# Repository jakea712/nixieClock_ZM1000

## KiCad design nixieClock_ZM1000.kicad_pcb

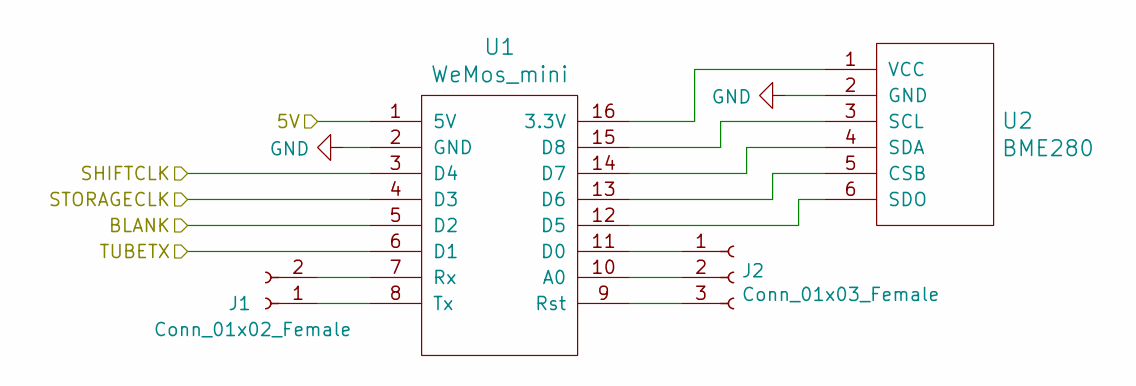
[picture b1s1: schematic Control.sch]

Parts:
J1: Conn_01x02_Female; PinHeader_1x02_P2.54mm_Vertical
J2: Conn_01x03_Female; PinHeader_1x03_P2.54mm_Vertical
U1: WeMos_mini; D1_mini_board
U2: BME280

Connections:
unnamed: J1.1, U1.8 (Tx)
unnamed: J1.2, U1.7 (Rx)
unnamed: J2.1, U1.11 (D0)
unnamed: J2.2, U1.10 (A0)
unnamed: J2.3, U1.9 (Rst)
unnamed: U1.12 (D5), U2.6 (SDO)
unnamed: U1.13 (D6), U2.5 (CSB)
unnamed: U1.14 (D7), U2.4 (SDA)
unnamed: U1.15 (D8), U2.3 (SCL)
unnamed: U1.16 (3.3V), U2.1 (VCC)

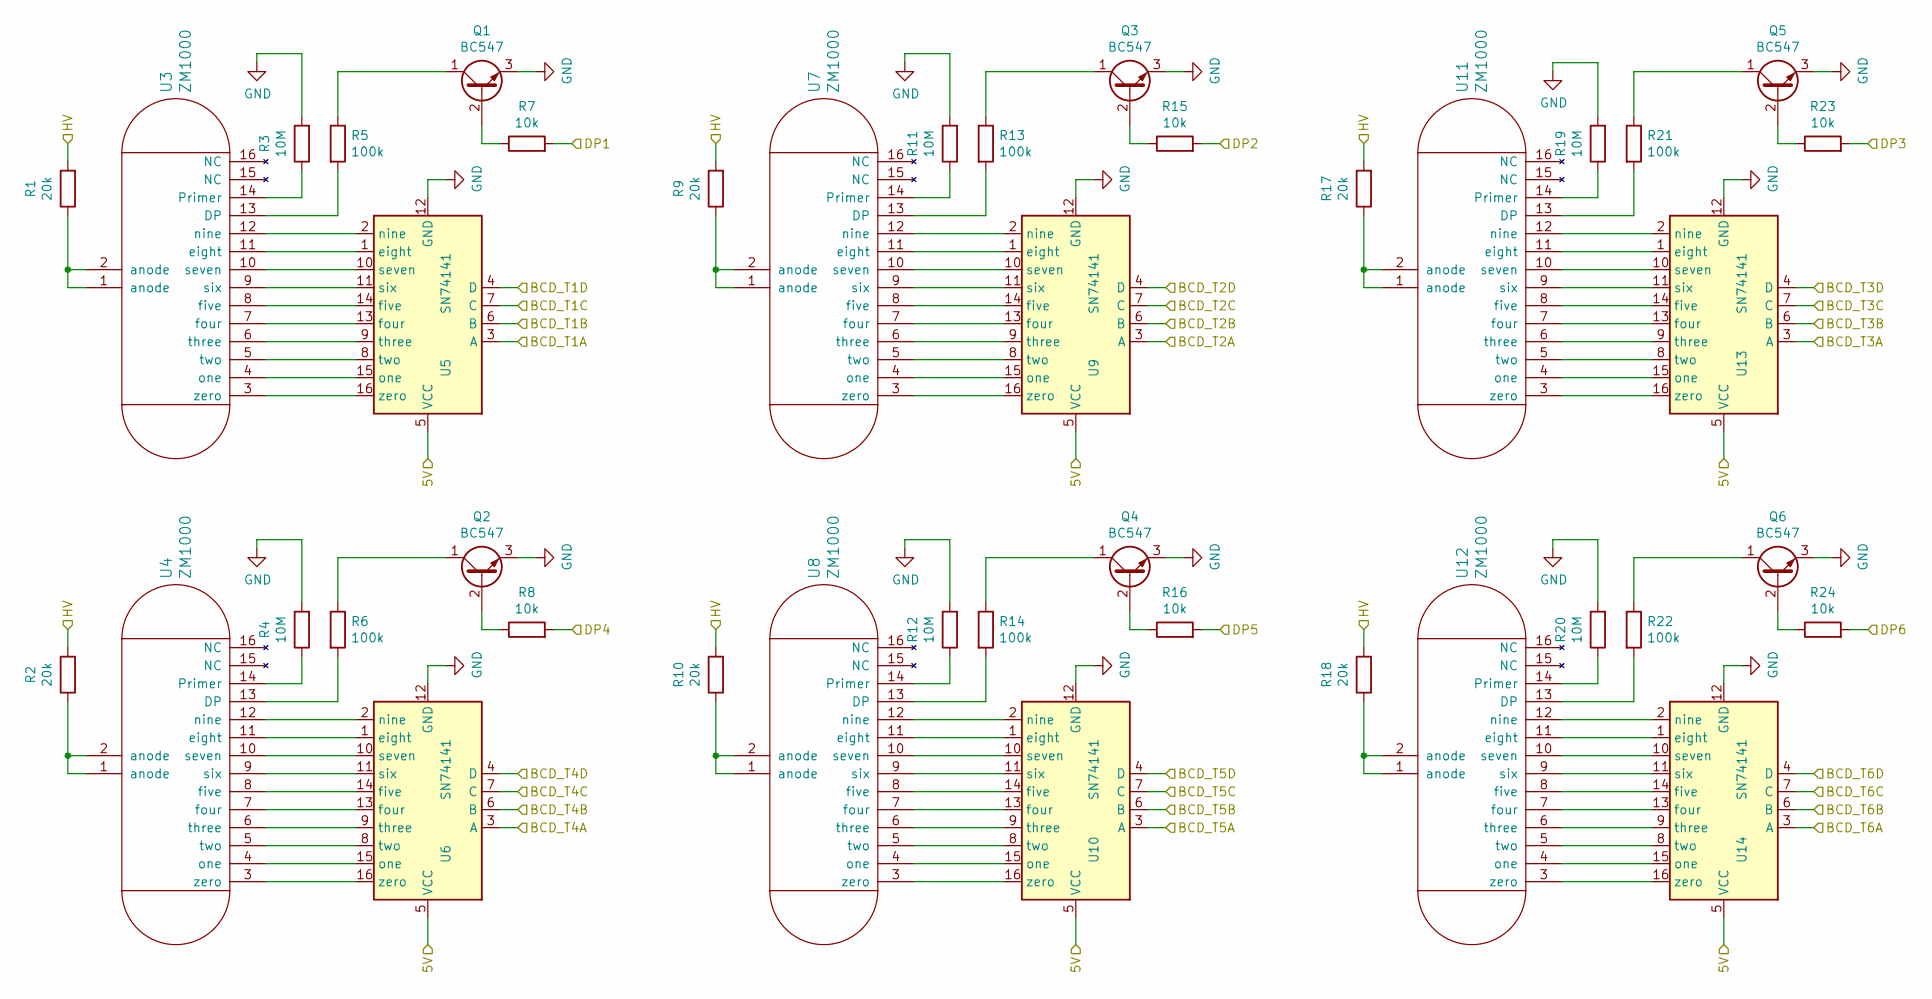
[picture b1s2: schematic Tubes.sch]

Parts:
Q1, Q2, Q3, Q4, Q5, Q6: BC547; TO-92_Inline
R1, R2, R9, R10, R17, R18: 20k; R_Axial_DIN0207_L6.3mm_D2.5mm_P10.16mm_Horizontal
R3, R4, R11, R12, R19, R20: 10M; R_Axial_DIN0207_L6.3mm_D2.5mm_P10.16mm_Horizontal
R5, R6, R13, R14, R21, R22: 100k; R_Axial_DIN0207_L6.3mm_D2.5mm_P10.16mm_Horizontal
R7, R8, R15, R16, R23, R24: 10k; R_Axial_DIN0207_L6.3mm_D2.5mm_P10.16mm_Horizontal
U3, U4, U7, U8, U11, U12: ZM1000; Nixie_ZM1000
U5, U6, U9, U10, U13, U14: SN74141; DIP-16_W7.62mm

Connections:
/PSU/HV: R1.2, R2.2, R9.2, R10.2, R17.2, R18.2; also elsewhere on the board
/Shift Registers/BCD_T1A: U5.3 (A); also elsewhere on the board
/Shift Registers/BCD_T1B: U5.6 (B); also elsewhere on the board
/Shift Registers/BCD_T1C: U5.7 (C); also elsewhere on the board
/Shift Registers/BCD_T1D: U5.4 (D); also elsewhere on the board
/Shift Registers/BCD_T2A: U9.3 (A); also elsewhere on the board
/Shift Registers/BCD_T2B: U9.6 (B); also elsewhere on the board
/Shift Registers/BCD_T2C: U9.7 (C); also elsewhere on the board
/Shift Registers/BCD_T2D: U9.4 (D); also elsewhere on the board
/Shift Registers/BCD_T3A: U13.3 (A); also elsewhere on the board
/Shift Registers/BCD_T3B: U13.6 (B); also elsewhere on the board
/Shift Registers/BCD_T3C: U13.7 (C); also elsewhere on the board
/Shift Registers/BCD_T3D: U13.4 (D); also elsewhere on the board
/Shift Registers/BCD_T4A: U6.3 (A); also elsewhere on the board
/Shift Registers/BCD_T4B: U6.6 (B); also elsewhere on the board
/Shift Registers/BCD_T4C: U6.7 (C); also elsewhere on the board
/Shift Registers/BCD_T4D: U6.4 (D); also elsewhere on the board
/Shift Registers/BCD_T5A: U10.3 (A); also elsewhere on the board
/Shift Registers/BCD_T5B: U10.6 (B); also elsewhere on the board
/Shift Registers/BCD_T5C: U10.7 (C); also elsewhere on the board
/Shift Registers/BCD_T5D: U10.4 (D); also elsewhere on the board
/Shift Registers/BCD_T6A: U14.3 (QD); also elsewhere on the board
/Shift Registers/BCD_T6B: U14.6 (QG); also elsewhere on the board
/Shift Registers/BCD_T6C: U14.7 (QH); also elsewhere on the board
/Shift Registers/BCD_T6D: U14.4 (QE); also elsewhere on the board
/Shift Registers/DP1: R7.2; also elsewhere on the board
/Shift Registers/DP2: R15.2; also elsewhere on the board
/Shift Registers/DP3: R23.2; also elsewhere on the board
/Shift Registers/DP4: R8.2; also elsewhere on the board
/Shift Registers/DP5: R16.2; also elsewhere on the board
/Shift Registers/DP6: R24.2; also elsewhere on the board
unnamed: Q1.1 (C), R5.1
unnamed: Q1.2 (B), R7.1
unnamed: Q2.1 (C), R6.1
unnamed: Q2.2 (B), R8.1
unnamed: Q3.1 (C), R13.1
unnamed: Q3.2 (B), R15.1
unnamed: Q4.1 (C), R14.1
unnamed: Q4.2 (B), R16.1
unnamed: Q5.1 (C), R21.1
unnamed: Q5.2 (B), R23.1
unnamed: Q6.1 (C), R22.1
unnamed: Q6.2 (B), R24.1
unnamed: R1.1, U3.1 (anode), U3.2 (anode)
unnamed: R2.1, U4.1 (anode), U4.2 (anode)
unnamed: R3.1, U3.14 (Primer)
unnamed: R4.1, U4.14 (Primer)
unnamed: R5.2, U3.13 (DP)
unnamed: R6.2, U4.13 (DP)
unnamed: R9.1, U7.1 (anode), U7.2 (anode)
unnamed: R10.1, U8.1 (anode), U8.2 (anode)
unnamed: R11.1, U7.14 (Primer)
unnamed: R12.1, U8.14 (Primer)
unnamed: R13.2, U7.13 (DP)
unnamed: R14.2, U8.13 (DP)
unnamed: R17.1, U11.1 (anode), U11.2 (anode)
unnamed: R18.1, U12.1 (anode), U12.2 (anode)
unnamed: R19.1, U11.14 (Primer)
unnamed: R20.1, U12.14 (Primer)
unnamed: R21.2, U11.13 (DP)
unnamed: R22.2, U12.13 (DP)
unnamed: U3.3 (zero), U5.16 (zero)
unnamed: U3.4 (one), U5.15 (one)
unnamed: U3.5 (two), U5.8 (two)
unnamed: U3.6 (three), U5.9 (three)
unnamed: U3.7 (four), U5.13 (four)
unnamed: U3.8 (five), U5.14 (five)
unnamed: U3.9 (six), U5.11 (six)
unnamed: U3.10 (seven), U5.10 (seven)
unnamed: U3.11 (eight), U5.1 (eight)
unnamed: U3.12 (nine), U5.2 (nine)
unnamed: U4.3 (zero), U6.16 (zero)
unnamed: U4.4 (one), U6.15 (one)
unnamed: U4.5 (two), U6.8 (two)
unnamed: U4.6 (three), U6.9 (three)
unnamed: U4.7 (four), U6.13 (four)
unnamed: U4.8 (five), U6.14 (five)
unnamed: U4.9 (six), U6.11 (six)
unnamed: U4.10 (seven), U6.10 (seven)
unnamed: U4.11 (eight), U6.1 (eight)
unnamed: U4.12 (nine), U6.2 (nine)
unnamed: U7.3 (zero), U9.16 (zero)
unnamed: U7.4 (one), U9.15 (one)
unnamed: U7.5 (two), U9.8 (two)
unnamed: U7.6 (three), U9.9 (three)
unnamed: U7.7 (four), U9.13 (four)
unnamed: U7.8 (five), U9.14 (five)
unnamed: U7.9 (six), U9.11 (six)
unnamed: U7.10 (seven), U9.10 (seven)
unnamed: U7.11 (eight), U9.1 (eight)
unnamed: U7.12 (nine), U9.2 (nine)
unnamed: U8.11 (eight), U10.1 (eight)
unnamed: U8.12 (nine), U10.2 (nine)
unnamed: U8.5 (two), U10.8 (two)
unnamed: U8.6 (three), U10.9 (three)
unnamed: U8.10 (seven), U10.10 (seven)
unnamed: U8.9 (six), U10.11 (six)
unnamed: U8.7 (four), U10.13 (four)
unnamed: U8.8 (five), U10.14 (five)
unnamed: U8.4 (one), U10.15 (one)
unnamed: U8.3 (zero), U10.16 (zero)
unnamed: U11.3 (zero), U13.16 (zero)
unnamed: U11.4 (one), U13.15 (one)
unnamed: U11.5 (two), U13.8 (two)
unnamed: U11.6 (three), U13.9 (three)
unnamed: U11.7 (four), U13.13 (four)
unnamed: U11.8 (five), U13.14 (five)
unnamed: U11.9 (six), U13.11 (six)
unnamed: U11.10 (seven), U13.10 (seven)
unnamed: U11.11 (eight), U13.1 (eight)
unnamed: U11.12 (nine), U13.2 (nine)
unnamed: U12.4 (one), U14.15 (QA)
unnamed: U12.8 (five), U14.14 (SER)
unnamed: U12.11 (eight), U14.1 (QB)
unnamed: U12.12 (nine), U14.2 (QC)

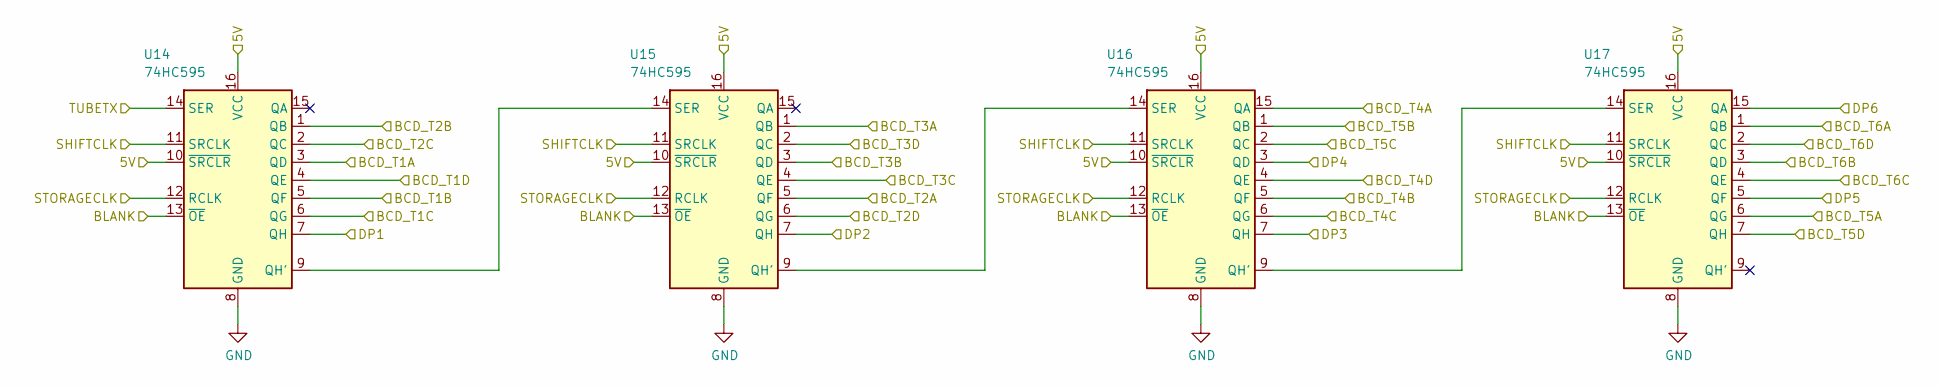
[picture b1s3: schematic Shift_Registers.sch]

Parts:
U14, U15, U16, U17: 74HC595; SOIC-16_3.9x9.9mm_P1.27mm

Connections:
/Shift Registers/BCD_T1A: U15.3 (QD); also elsewhere on the board
/Shift Registers/BCD_T1B: U15.5 (QF); also elsewhere on the board
/Shift Registers/BCD_T1C: U15.6 (QG); also elsewhere on the board
/Shift Registers/BCD_T1D: U15.4 (QE); also elsewhere on the board
/Shift Registers/BCD_T2A: U16.5 (QF); also elsewhere on the board
/Shift Registers/BCD_T2B: U15.1 (QB); also elsewhere on the board
/Shift Registers/BCD_T2C: U15.2 (QC); also elsewhere on the board
/Shift Registers/BCD_T2D: U16.6 (QG); also elsewhere on the board
/Shift Registers/BCD_T3A: U16.1 (QB); also elsewhere on the board
/Shift Registers/BCD_T3B: U16.3 (QD); also elsewhere on the board
/Shift Registers/BCD_T3C: U16.4 (QE); also elsewhere on the board
/Shift Registers/BCD_T3D: U16.2 (QC); also elsewhere on the board
/Shift Registers/BCD_T4A: U17.15 (QA); also elsewhere on the board
/Shift Registers/BCD_T4B: U17.5 (QF); also elsewhere on the board
/Shift Registers/BCD_T4C: U17.6 (QG); also elsewhere on the board
/Shift Registers/BCD_T4D: U17.4 (QE); also elsewhere on the board
/Shift Registers/BCD_T5B: U17.1 (QB); also elsewhere on the board
/Shift Registers/BCD_T5C: U17.2 (QC); also elsewhere on the board
/Shift Registers/BCD_T6A: U14.3 (QD); also elsewhere on the board
/Shift Registers/BCD_T6B: U14.6 (QG); also elsewhere on the board
/Shift Registers/BCD_T6C: U14.7 (QH); also elsewhere on the board
/Shift Registers/BCD_T6D: U14.4 (QE); also elsewhere on the board
/Shift Registers/DP1: U15.7 (QH); also elsewhere on the board
/Shift Registers/DP2: U16.7 (QH); also elsewhere on the board
/Shift Registers/DP3: U17.7 (QH); also elsewhere on the board
/Shift Registers/DP4: U17.3 (QD); also elsewhere on the board
unnamed 132: U14.15 (QA); also elsewhere on the board
unnamed 133: U14.14 (SER); also elsewhere on the board
unnamed 134: U14.1 (QB); also elsewhere on the board
unnamed 135: U14.2 (QC); also elsewhere on the board
unnamed: U15.9 (QH'), U16.14 (SER)
unnamed: U16.9 (QH'), U17.14 (SER)
unnamed 140: U17.9 (QH'); also elsewhere on the board

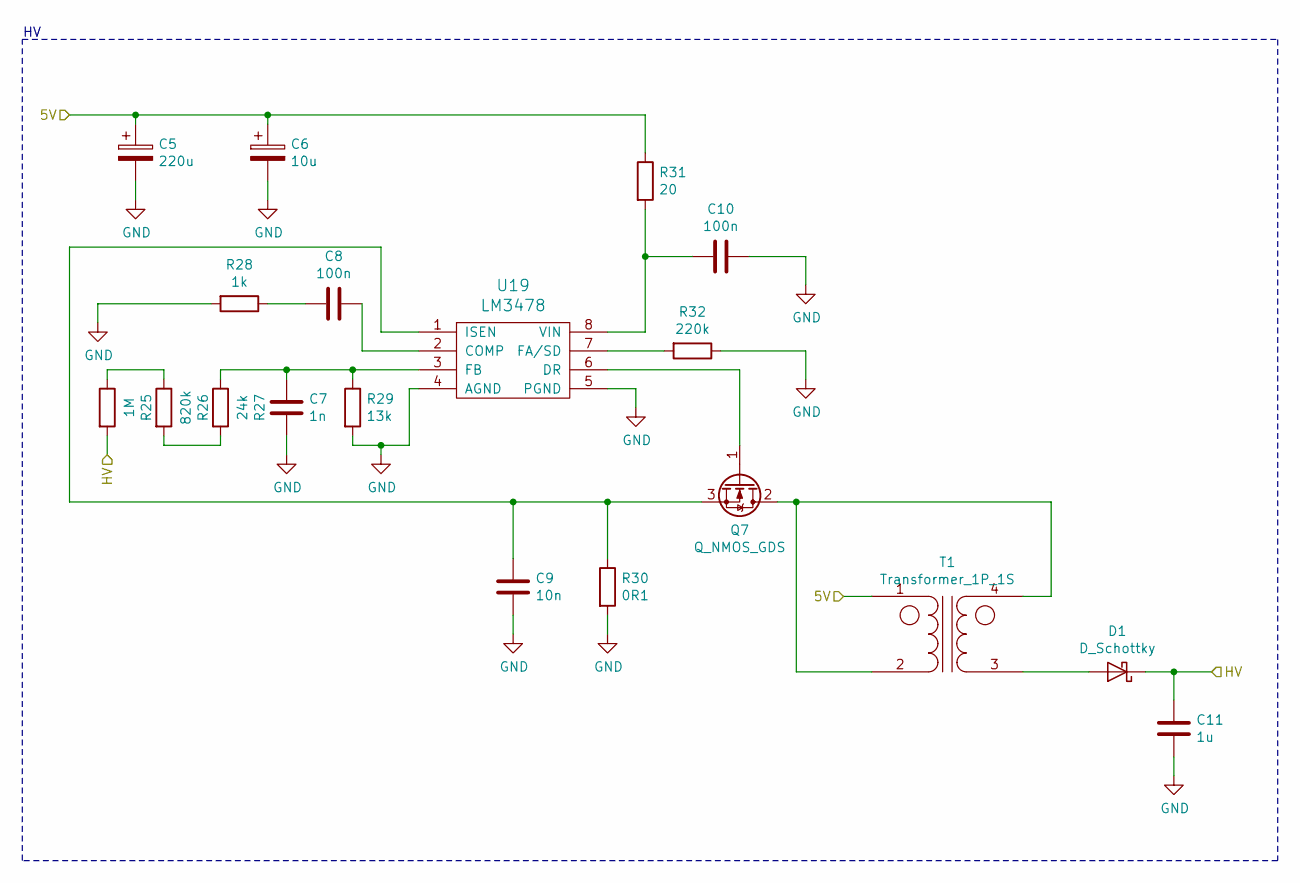
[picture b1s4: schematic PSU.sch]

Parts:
C5: 220u; CP_Radial_D5.0mm_P2.00mm
C6: 10u; CP_Radial_D4.0mm_P1.50mm
C7: 1n; C_Disc_D3.8mm_W2.6mm_P2.50mm
C8: 100n; C_Disc_D3.8mm_W2.6mm_P2.50mm
C9: 10n; C_Disc_D3.8mm_W2.6mm_P2.50mm
C10: 100n; C_Disc_D5.0mm_W2.5mm_P2.50mm
C11: 1u; CP_Radial_D6.3mm_P2.50mm
D1: D_Schottky; D_DO-41_SOD81_P10.16mm_Horizontal
Q7: Q_NMOS_GDS; TO-220-3_Horizontal_TabDown
R25: 1M; R_Axial_DIN0207_L6.3mm_D2.5mm_P10.16mm_Horizontal
R26: 820k; R_Axial_DIN0207_L6.3mm_D2.5mm_P10.16mm_Horizontal
R27: 24k; R_Axial_DIN0207_L6.3mm_D2.5mm_P10.16mm_Horizontal
R28: 1k; R_Axial_DIN0207_L6.3mm_D2.5mm_P10.16mm_Horizontal
R29: 13k; R_Axial_DIN0207_L6.3mm_D2.5mm_P10.16mm_Horizontal
R30: 0R1; R_Axial_DIN0207_L6.3mm_D2.5mm_P10.16mm_Horizontal
R31: 20; R_Axial_DIN0207_L6.3mm_D2.5mm_P10.16mm_Horizontal
R32: 220k; R_Axial_DIN0207_L6.3mm_D2.5mm_P10.16mm_Horizontal
T1: Transformer_1P_1S; Transformer_LPR6235
U19: LM3478; VSSOP-8_3.0x3.0mm_P0.65mm

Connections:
/PSU/HV: C11.1, D1.1 (K), R25.2; also elsewhere on the board
unnamed: C7.1, R27.1, R29.1, U19.3 (FB)
unnamed: C8.1, U19.2 (COMP)
unnamed: C8.2, R28.1
unnamed: C9.1, Q7.3 (S), R30.1, U19.1 (ISEN)
unnamed: C10.2, R31.2, U19.8 (VIN)
unnamed: D1.2 (A), T1.3 (SA)
unnamed: Q7.1 (G), U19.6 (DR)
unnamed: Q7.2 (D), T1.2 (AB), T1.4 (SB)
unnamed: R25.1, R26.1
unnamed: R26.2, R27.2
unnamed: R32.2, U19.7 (FA/SD)

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
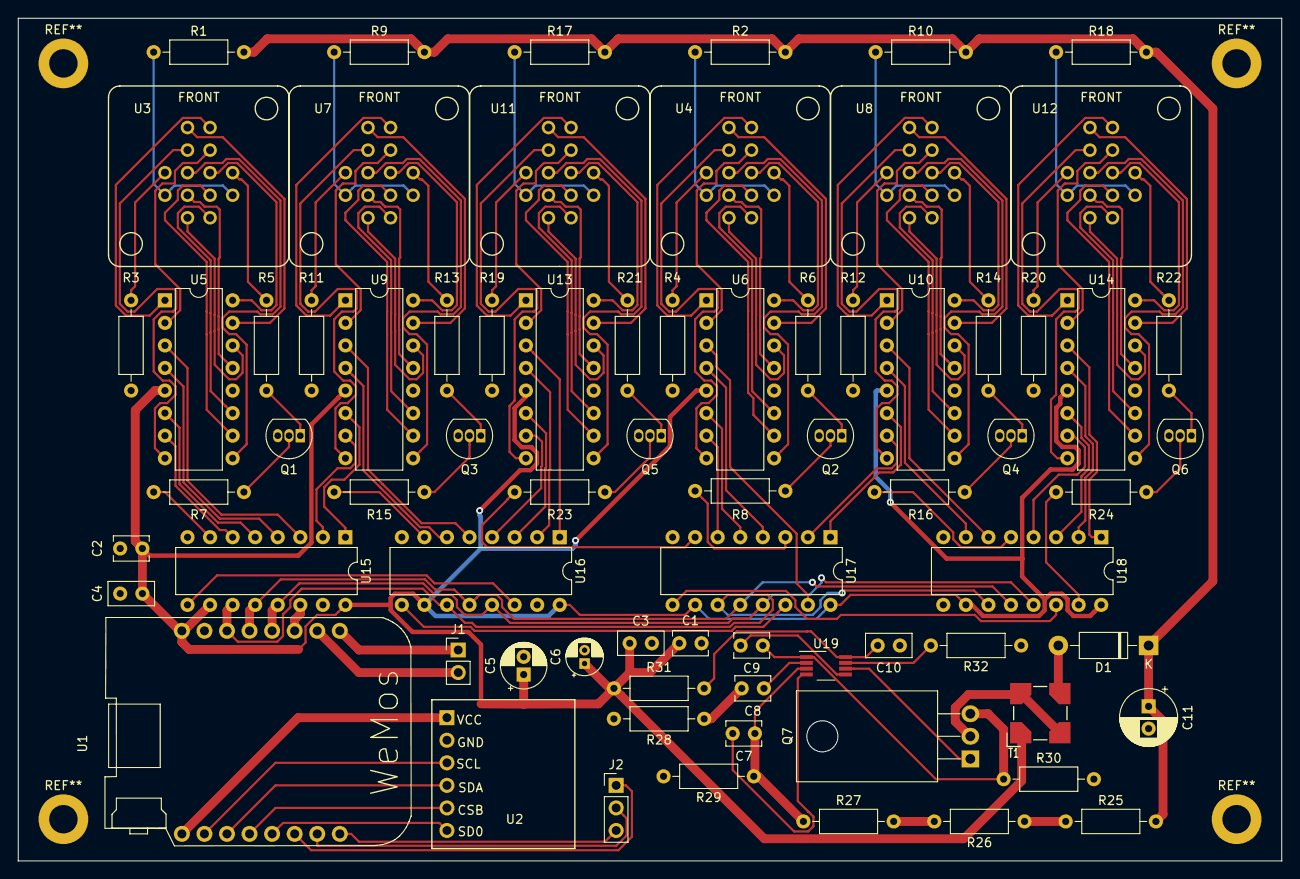
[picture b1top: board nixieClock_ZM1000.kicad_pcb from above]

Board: 2 copper layers, 142.2 x 94.9 mm, 73 parts (0 on the bottom side), 151 nets.

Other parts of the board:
C1, C2: 10n; C_Disc_D3.8mm_W2.6mm_P2.50mm
C3, C4: 100n; C_Disc_D5.0mm_W2.5mm_P2.50mm
U18: 74HC595; DIP-16_W7.62mm

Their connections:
/Shift Registers/BCD_T5A: U18.6; also elsewhere on the board
/Shift Registers/BCD_T5D: U18.7; also elsewhere on the board
/Shift Registers/BCD_T6A: U18.1; also elsewhere on the board
/Shift Registers/BCD_T6B: U18.3; also elsewhere on the board
/Shift Registers/BCD_T6C: U18.4; also elsewhere on the board
/Shift Registers/BCD_T6D: U18.2; also elsewhere on the board
/Shift Registers/DP5: U18.5; also elsewhere on the board
/Shift Registers/DP6: U18.15; also elsewhere on the board
unnamed 140: U18.14; also elsewhere on the board

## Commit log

2019-09-23 Inserted PSU
2019-09-23 Added sheets
2019-09-25 no message
2019-09-30 Finished draft schema
2019-10-03 Moved DPs to shift register as not enough IO
2019-10-03 Finished schema and started PCB layout
2019-10-04 90% routed
2019-10-05 Completed layout inc optimisation of data pattern for shift registers
2019-10-05 Added more decoupling
2019-10-08 Update to PSU
2019-10-09 Corrected errors on PSU
2019-10-14 Szitched to DIP shift registers, added BME280
2019-10-18 Final pending check
2020-04-06 Fixed tube footprints and rerouted
